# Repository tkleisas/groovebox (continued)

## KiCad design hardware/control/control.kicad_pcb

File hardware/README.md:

# NSR-1 hardware — rev B2

**NSR-1 is the active hardware target.** NSR-2 is a deferred reference
design. The platform mission, support tiers, and the separate-carrier-per-SBC
policy are in [`../docs/mission.md`](../docs/mission.md).

The NSR-1 platform has four boards:

| Board | Spec | Status |
|---|---|---|
| Keyboard | [`netlist-spec.md`](netlist-spec.md) | routed, 0 DRC, EMD-verified |
| Control | [`netlist-spec.md`](netlist-spec.md) | routed, 0 DRC, EMD-verified |
| Brain carrier (Pi Zero 2W) | [`brain/netlist-spec.md`](brain/netlist-spec.md) | 110 × 90, routed, 0 unconnected, 4× M3 |
| Power/battery | [`power/netlist-spec.md`](power/netlist-spec.md) | 100 × 70, 4-layer, routed except 4 airwires |

The control and keyboard boards are the existing rev B2 design. The brain
carrier and power board are new platform boards; their specs are the source of
truth for those boards. A future SBC gets its own carrier under `hardware/`,
not an adapter on the Pi carrier.

This hardware is imported and packaged by
[ElectroMechanicalDesigner](https://github.com/tkleisas/ElectroMechanicalDesigner);
see [`../README.md`](../README.md#electromechanicaldesigner-integration) and
`hardware/tools/verify_emd.py`.

Source of truth for the control/keyboard: [`netlist-spec.md`](netlist-spec.md).
The firmware contract is `panel-fw/src/board_config.h`; change both together.

## Generated schematics

The control and keyboard schematics are generated. Do not hand-edit the
`.kicad_sch` files while the generator is active; change the generator and
regenerate.

```bash
python3 hardware/tools/gen_schematics.py control keyboard brain
python3 hardware/tools/verify_schematics.py
# In the KiCad 10 container:
python3 hardware/tools/place_control.py
python3 hardware/tools/place_keyboard.py
python3 hardware/tools/add_ground_pour.py control
python3 hardware/tools/add_ground_pour.py keyboard
python3 hardware/tools/verify_fit.py
# New platform outlines (run in the KiCad container):
python3 hardware/tools/make_platform_outlines.py
# Add header/connector silkscreen labels once, after routing:
python3 hardware/tools/add_board_labels.py control keyboard brain power
```

`gen_schematics.py` uses the KiCad 10 symbol definitions embedded in the
checked-in NSR-2 schematics for control/keyboard/brain. The power board also
needs the installed KiCad symbol libraries, so generate it inside the KiCad
container with `-e KICAD_SYMBOL_DIR=/usr/share/kicad/symbols`.
`verify_schematics.py` checks pin coverage, key/encoder/analog nets, I²C
endpoints, address straps, LED ROW/COM grouping, and power endpoints.

Export netlists and validate them with EMD:

```bash
python3 hardware/tools/export_netlist.py
# power netlist needs the KiCad symbol directory:
docker run --rm -v "$PWD:/work" -w /work \
  -e KICAD_SYMBOL_DIR=/usr/share/kicad/symbols kicad/kicad:10.0 \
  python3 hardware/tools/export_netlist.py --board power
python3 hardware/tools/verify_emd.py --emd /path/to/emd
python3 hardware/tools/verify_emd.py --package-dir hardware/emd-packages \
  --combined hardware/emd-packages/groovebox.json
```

Check the firmware map against the five-expander contract:

```bash
gcc -std=c11 -Ipanel-fw/src hardware/tools/check_board_config.c -o /tmp/check_board_config
/tmp/check_board_config
```

The control/keyboard board outlines are rev B2: control 130 × 100 mm,
keyboard 356 × 80 mm. Both boards are placed, routed, and checked. The MX
hot-swap footprint is vendored from the keyswitch-kicad-library (`nsr1_fp`,
CC-BY-SA 4.0) and is assigned to all 45 switch symbols.

The brain carrier is the first SBC-specific board. It is a Raspberry Pi Zero
2W carrier by design; Radxa Zero 3W and Orange Pi Zero 3W would each get a
separate carrier and validation effort. The power board is common to all
carriers. Brain carrier: 110 × 90 mm, routed, 0 unconnected, EMD-valid
netlist. Power board: 100 × 70 mm, 4-layer, routed except four rev A airwires
(two BAT_NEG, two SCL). Start from their netlist specs.

The Pico uses `Module:RaspberryPi_Pico_Common_THT` (2×20, 17.78 mm row
spacing, four mounting holes). The Pi Zero uses
`Module:Raspberry_Pi_Zero_Socketed_THT_FaceDown_MountingHoles` (2×20, 2.54 mm
row spacing, mounting holes). Both headers carry silkscreen pin numbers; the
Pico also carries GPIO names.

## KiCad checks

With KiCad 10 in Docker:

```bash
docker run --rm -v "$PWD:/work" -w /work kicad/kicad:10.0 \
  kicad-cli sch erc hardware/control/control.kicad_sch \
  --output /work/control-erc.json --format json --severity-all
```

Current result: **0 ERC errors** for control, keyboard, brain, and power.
Expected warnings are `lib_symbol_mismatch` from the embedded symbol copies
(cosmetic). Routed control/keyboard/brain DRC is clean with 0 unconnected
items; the power board is routed except four rev A airwires (two `BAT_NEG`, two `SCL`).

Generate Gerbers, drill files, position CSV, BOM, STEP, stats, and zip
archives with:

```bash
hardware/tools/export_fabrication.sh
```

Outputs land in `hardware/fabrication/` and are gitignored; regenerate them
from the routed boards when needed. The STEP export defaults to a board-only
model because the KiCad container does not ship the 3D model library. Set
`STEP_FLAGS="--subst-models"` when `kicad-packages3d` is mounted or installed.

## Current scope

- **Control board:** Pico, 2× ADS1115, 2× MCP23017, 8 encoder connectors,
  CUT/RES pots, slider, joystick, 10 function-key connectors, joystick switch,
  keyboard/UART links.
- **Keyboard board:** 45 MX hot-swap sockets (29 piano/shift + 16 step row),
  3× MCP23017, HT16K33, 32 LEDs.
- **Control board:** placed and routed with 0 DRC violations and 0 unconnected
  items. Routing was done with Freerouting 2.5 via Specctra DSN/SES at
  0.15 mm clearance and a 0.1 mm minimum track width; the board grew to 130 × 100 mm to
  clear the eight encoder headers. Four M3 mounting-hole footprints are
  present for EMD mechanical ports.
- **Keyboard board:** all 45 switches, 32 LEDs, 32 resistors, 3 key expanders,
  HT16K33, link, and decoupling placed with
  `hardware/tools/place_keyboard.py`, then routed with Freerouting; DRC
  reports 0 violations and 0 unconnected items. Four M3 mounting-hole
  footprints are present for EMD mechanical ports.
- **Ground pour:** control, keyboard, brain, and power boards have a filled
  B.Cu GND zone.
- **Brain carrier:** Raspberry Pi Zero 2W carrier rev A is 110 × 90 mm,
  routed with 0 unconnected items, 0 ERC errors, and an EMD-valid netlist.
  See [`brain/netlist-spec.md`](brain/netlist-spec.md). It owns the Pi socket,
  Audio Injector Zero stack, display header, DIN MIDI, panel USB breakout, and
  5V input. It deliberately does not contain the battery charger or boost.
- **Power/battery board:** 100 × 70 mm, 4-layer, schematic generated and
  routed except four rev A airwires (two BAT_NEG, two SCL); see
  [`power/netlist-spec.md`](power/netlist-spec.md). It owns USB-C charging,
  1S pack protection/gauging, power switching, and the 5V/3A rail.
- **Mechanical envelope:** see [`enclosure-spec.md`](enclosure-spec.md);
  the 356 × 80 mm keyboard and under-mounted 130 × 100 mm control board fit the
  400 × 170 mm panel, with a ~32 mm internal stack. `verify_fit.py` checks this.
- **EMD package:** the combined project imports all four netlists/PCBs
  (control, keyboard, brain carrier, power), places them in the 400 × 170 mm
  envelope, validates 237 parts / 735 connections, and produces a verified
  package.
- **Enclosure:** printable tray and cutout faceplate are in
  [`enclosure/`](enclosure/README.md); rear I/O openings remain.
- **Power/thermal:** see [`power-thermal-review.md`](power-thermal-review.md).

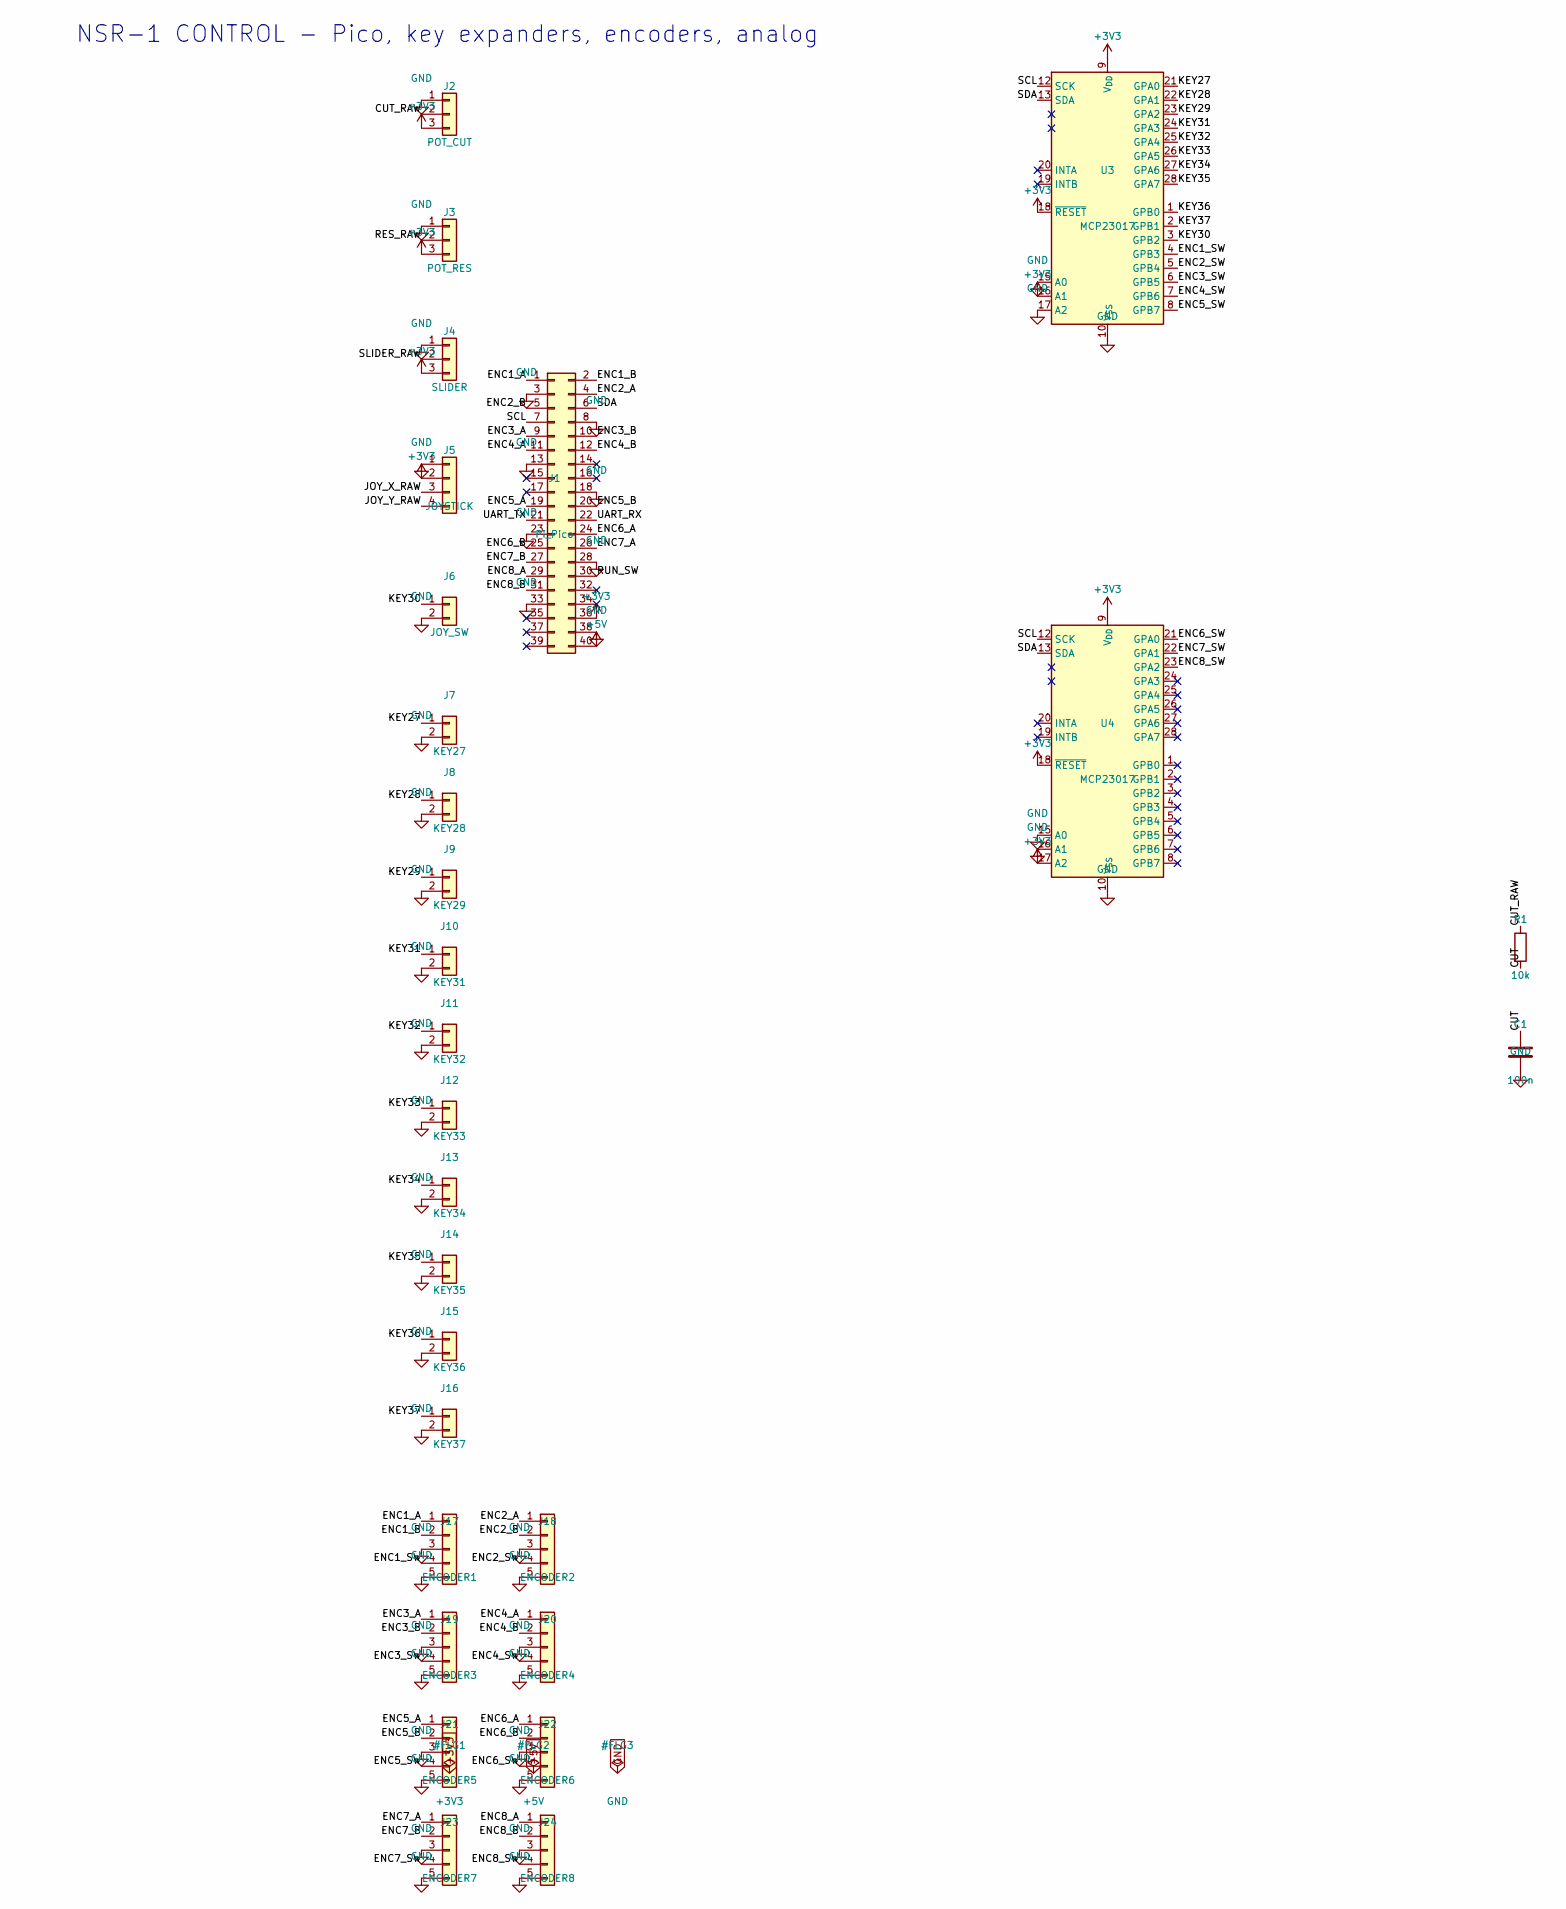
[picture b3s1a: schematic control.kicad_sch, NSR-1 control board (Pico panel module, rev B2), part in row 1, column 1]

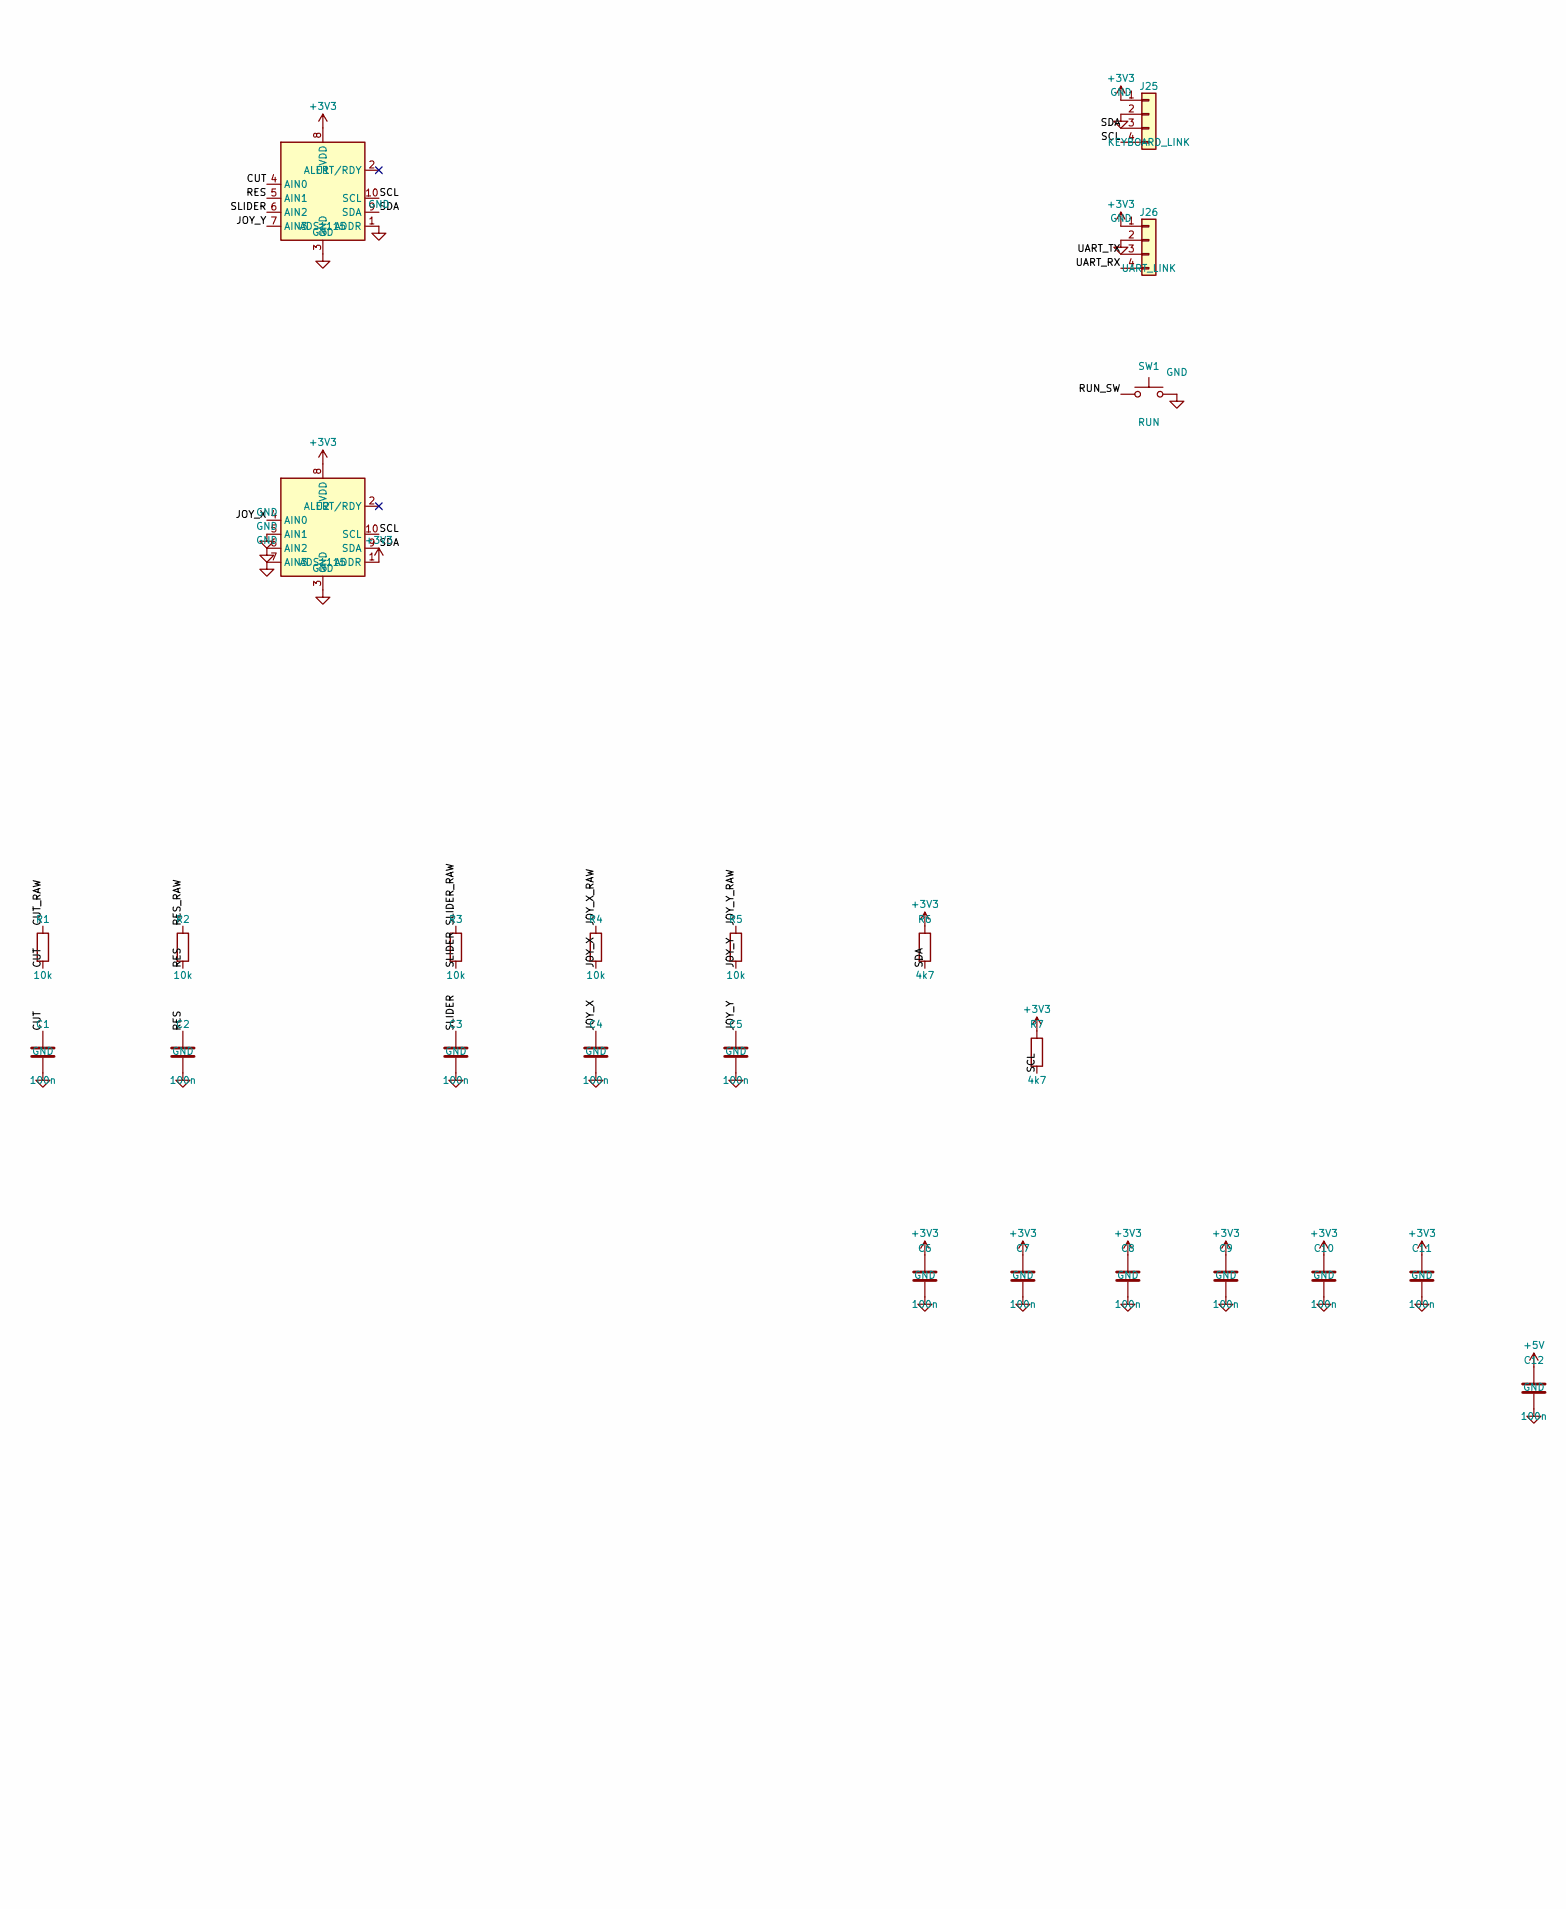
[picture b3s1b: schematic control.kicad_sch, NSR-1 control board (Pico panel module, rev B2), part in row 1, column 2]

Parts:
C1, C2, C3, C4, C5, C6, C7, C8, C9, C10, C11, C12: 100n; C_0805_2012Metric
J1: Pi_Pico; RaspberryPi_Pico_Common_THT
J2: POT_CUT; JST_XH_B3B-XH-A_1x03_P2.50mm_Vertical
J3: POT_RES; JST_XH_B3B-XH-A_1x03_P2.50mm_Vertical
J4: SLIDER; JST_XH_B3B-XH-A_1x03_P2.50mm_Vertical
J5: JOYSTICK; JST_XH_B4B-XH-A_1x04_P2.50mm_Vertical
J6: JOY_SW; JST_XH_B2B-XH-A_1x02_P2.50mm_Vertical
J7: KEY27; JST_XH_B2B-XH-A_1x02_P2.50mm_Vertical
J8: KEY28; JST_XH_B2B-XH-A_1x02_P2.50mm_Vertical
J9: KEY29; JST_XH_B2B-XH-A_1x02_P2.50mm_Vertical
J10: KEY31; JST_XH_B2B-XH-A_1x02_P2.50mm_Vertical
J11: KEY32; JST_XH_B2B-XH-A_1x02_P2.50mm_Vertical
J12: KEY33; JST_XH_B2B-XH-A_1x02_P2.50mm_Vertical
J13: KEY34; JST_XH_B2B-XH-A_1x02_P2.50mm_Vertical
J14: KEY35; JST_XH_B2B-XH-A_1x02_P2.50mm_Vertical
J15: KEY36; JST_XH_B2B-XH-A_1x02_P2.50mm_Vertical
J16: KEY37; JST_XH_B2B-XH-A_1x02_P2.50mm_Vertical
J17: ENCODER1; JST_XH_B5B-XH-A_1x05_P2.50mm_Vertical
J18: ENCODER2; JST_XH_B5B-XH-A_1x05_P2.50mm_Vertical
J19: ENCODER3; JST_XH_B5B-XH-A_1x05_P2.50mm_Vertical
J20: ENCODER4; JST_XH_B5B-XH-A_1x05_P2.50mm_Vertical
J21: ENCODER5; JST_XH_B5B-XH-A_1x05_P2.50mm_Vertical
J22: ENCODER6; JST_XH_B5B-XH-A_1x05_P2.50mm_Vertical
J23: ENCODER7; JST_XH_B5B-XH-A_1x05_P2.50mm_Vertical
J24: ENCODER8; JST_XH_B5B-XH-A_1x05_P2.50mm_Vertical
J25: KEYBOARD_LINK; JST_XH_B4B-XH-A_1x04_P2.50mm_Vertical
J26: UART_LINK; JST_XH_B4B-XH-A_1x04_P2.50mm_Vertical
R1, R2, R3, R4, R5: 10k; R_0805_2012Metric
R6, R7: 4k7; R_0805_2012Metric
SW1: RUN; SW_PUSH_6mm
U1, U2: ADS1115; MSOP-10_3x3mm_P0.5mm
U3, U4: MCP23017; SSOP-28_5.3x10.2mm_P0.65mm

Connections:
+3V3: C6.1, C7.1, C8.1, C9.1, C10.1, C11.1, J1.36, J2.3, J3.3, J4.3, J5.2, J25.1, J26.1, R6.1, R7.1, U1.8 (VDD), U2.1 (ADDR), U2.8 (VDD), U3.9 (V_{DD}), U3.16 (A1), U3.18 (~RESET), U4.9 (V_{DD}), U4.17 (A2), U4.18 (~RESET)
+5V: C12.1, J1.40
CUT: C1.1, R1.2, U1.4 (AIN0)
CUT_RAW: J2.2, R1.1
ENC1_A: J1.1, J17.1
ENC1_B: J1.2, J17.2
ENC1_SW: J17.4, U3.4 (GPB3)
ENC2_A: J1.4, J18.1
ENC2_B: J1.5, J18.2
ENC2_SW: J18.4, U3.5 (GPB4)
ENC3_A: J1.9, J19.1
ENC3_B: J1.10, J19.2
ENC3_SW: J19.4, U3.6 (GPB5)
ENC4_A: J1.11, J20.1
ENC4_B: J1.12, J20.2
ENC4_SW: J20.4, U3.7 (GPB6)
ENC5_A: J1.19, J21.1
ENC5_B: J1.20, J21.2
ENC5_SW: J21.4, U3.8 (GPB7)
ENC6_A: J1.24, J22.1
ENC6_B: J1.25, J22.2
ENC6_SW: J22.4, U4.21 (GPA0)
ENC7_A: J1.26, J23.1
ENC7_B: J1.27, J23.2
ENC7_SW: J23.4, U4.22 (GPA1)
ENC8_A: J1.29, J24.1
ENC8_B: J1.31, J24.2
ENC8_SW: J24.4, U4.23 (GPA2)
GND: C1.2, C2.2, C3.2, C4.2, C5.2, C6.2, C7.2, C8.2, C9.2, C10.2, C11.2, C12.2, J1.3, J1.8, J1.13, J1.18, J1.23, J1.28, J1.33, J1.38, J2.1, J3.1, J4.1, J5.1, J6.2, J7.2, J8.2, J9.2, J10.2, J11.2, J12.2, J13.2, J14.2, J15.2, J16.2, J17.3, J17.5, J18.3, J18.5, J19.3, J19.5, J20.3, J20.5, J21.3, J21.5, J22.3, J22.5, J23.3, J23.5, J24.3, J24.5, J25.2, J26.2, SW1.2, U1.1 (ADDR), U1.3 (GND), U2.3 (GND), U2.5 (AIN1), U2.6 (AIN2), U2.7 (AIN3), U3.10 (V_{SS}), U3.15 (A0), U3.17 (A2), U4.10 (V_{SS}), U4.15 (A0), U4.16 (A1)
JOY_X: C4.1, R4.2, U2.4 (AIN0)
JOY_X_RAW: J5.3, R4.1
JOY_Y: C5.1, R5.2, U1.7 (AIN3)
JOY_Y_RAW: J5.4, R5.1
KEY27: J7.1, U3.21 (GPA0)
KEY28: J8.1, U3.22 (GPA1)
KEY29: J9.1, U3.23 (GPA2)
KEY30: J6.1, U3.3 (GPB2)
KEY31: J10.1, U3.24 (GPA3)
KEY32: J11.1, U3.25 (GPA4)
KEY33: J12.1, U3.26 (GPA5)
KEY34: J13.1, U3.27 (GPA6)
KEY35: J14.1, U3.28 (GPA7)
KEY36: J15.1, U3.1 (GPB0)
KEY37: J16.1, U3.2 (GPB1)
RES: C2.1, R2.2, U1.5 (AIN1)
RES_RAW: J3.2, R2.1
RUN_SW: J1.30, SW1.1
SCL: J1.7, J25.4, R7.2, U1.10 (SCL), U2.10 (SCL), U3.12 (SCK), U4.12 (SCK)
SDA: J1.6, J25.3, R6.2, U1.9 (SDA), U2.9 (SDA), U3.13 (SDA), U4.13 (SDA)
SLIDER: C3.1, R3.2, U1.6 (AIN2)
SLIDER_RAW: J4.2, R3.1
UART_RX: J1.22, J26.4
UART_TX: J1.21, J26.3

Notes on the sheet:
NSR-1 CONTROL - Pico, key expanders, encoders, analog

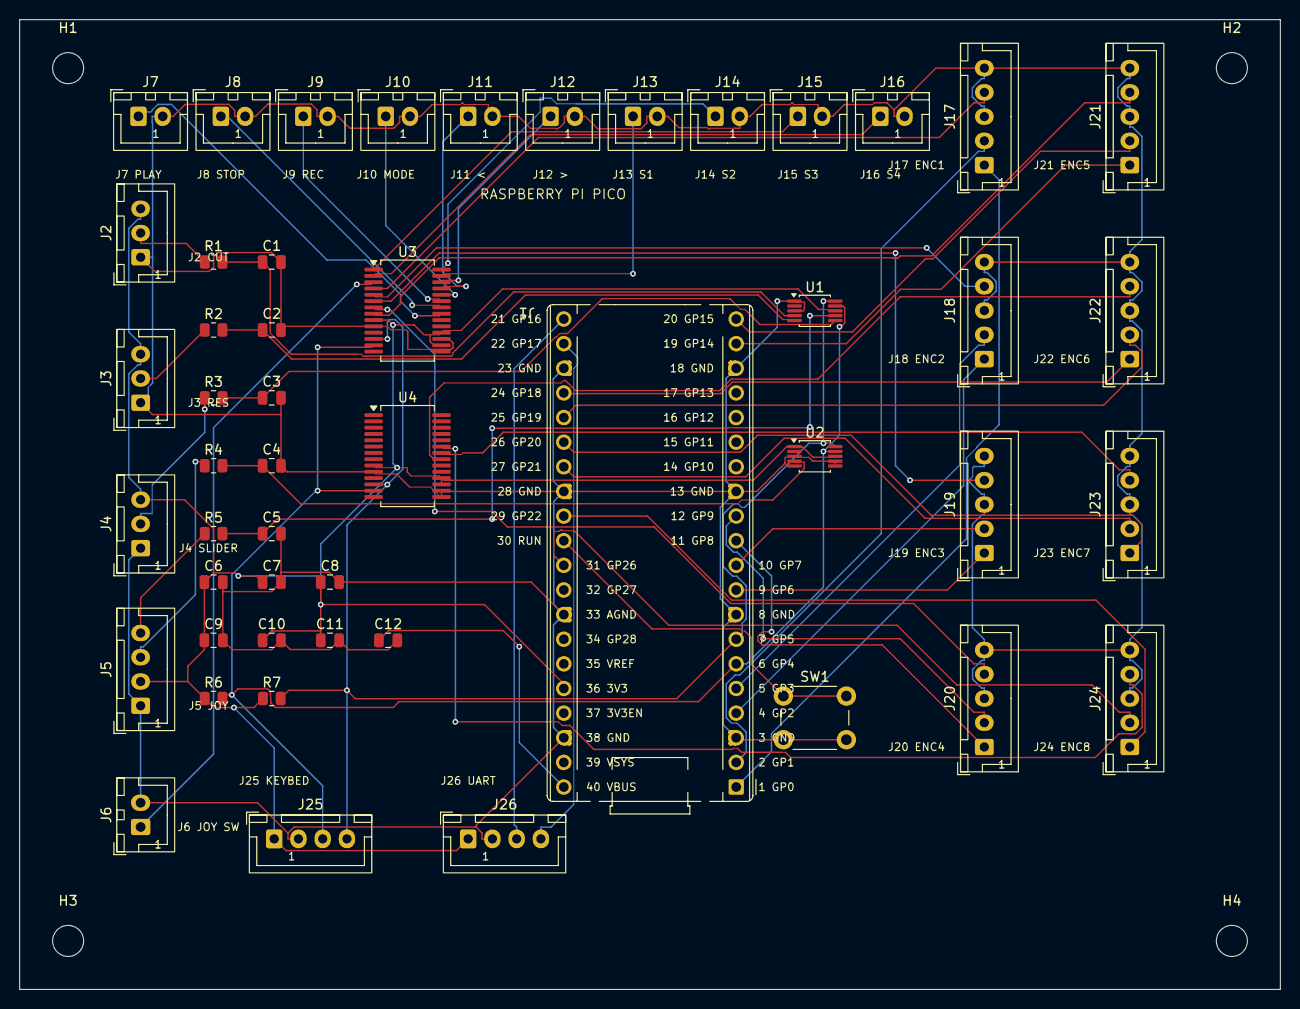
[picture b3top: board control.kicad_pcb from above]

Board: 2 copper layers, 130.0 x 100.0 mm, 54 parts (0 on the bottom side), 53 nets.

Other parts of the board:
H1, H2, H3, H4: MountingHole_3.2mm_M3

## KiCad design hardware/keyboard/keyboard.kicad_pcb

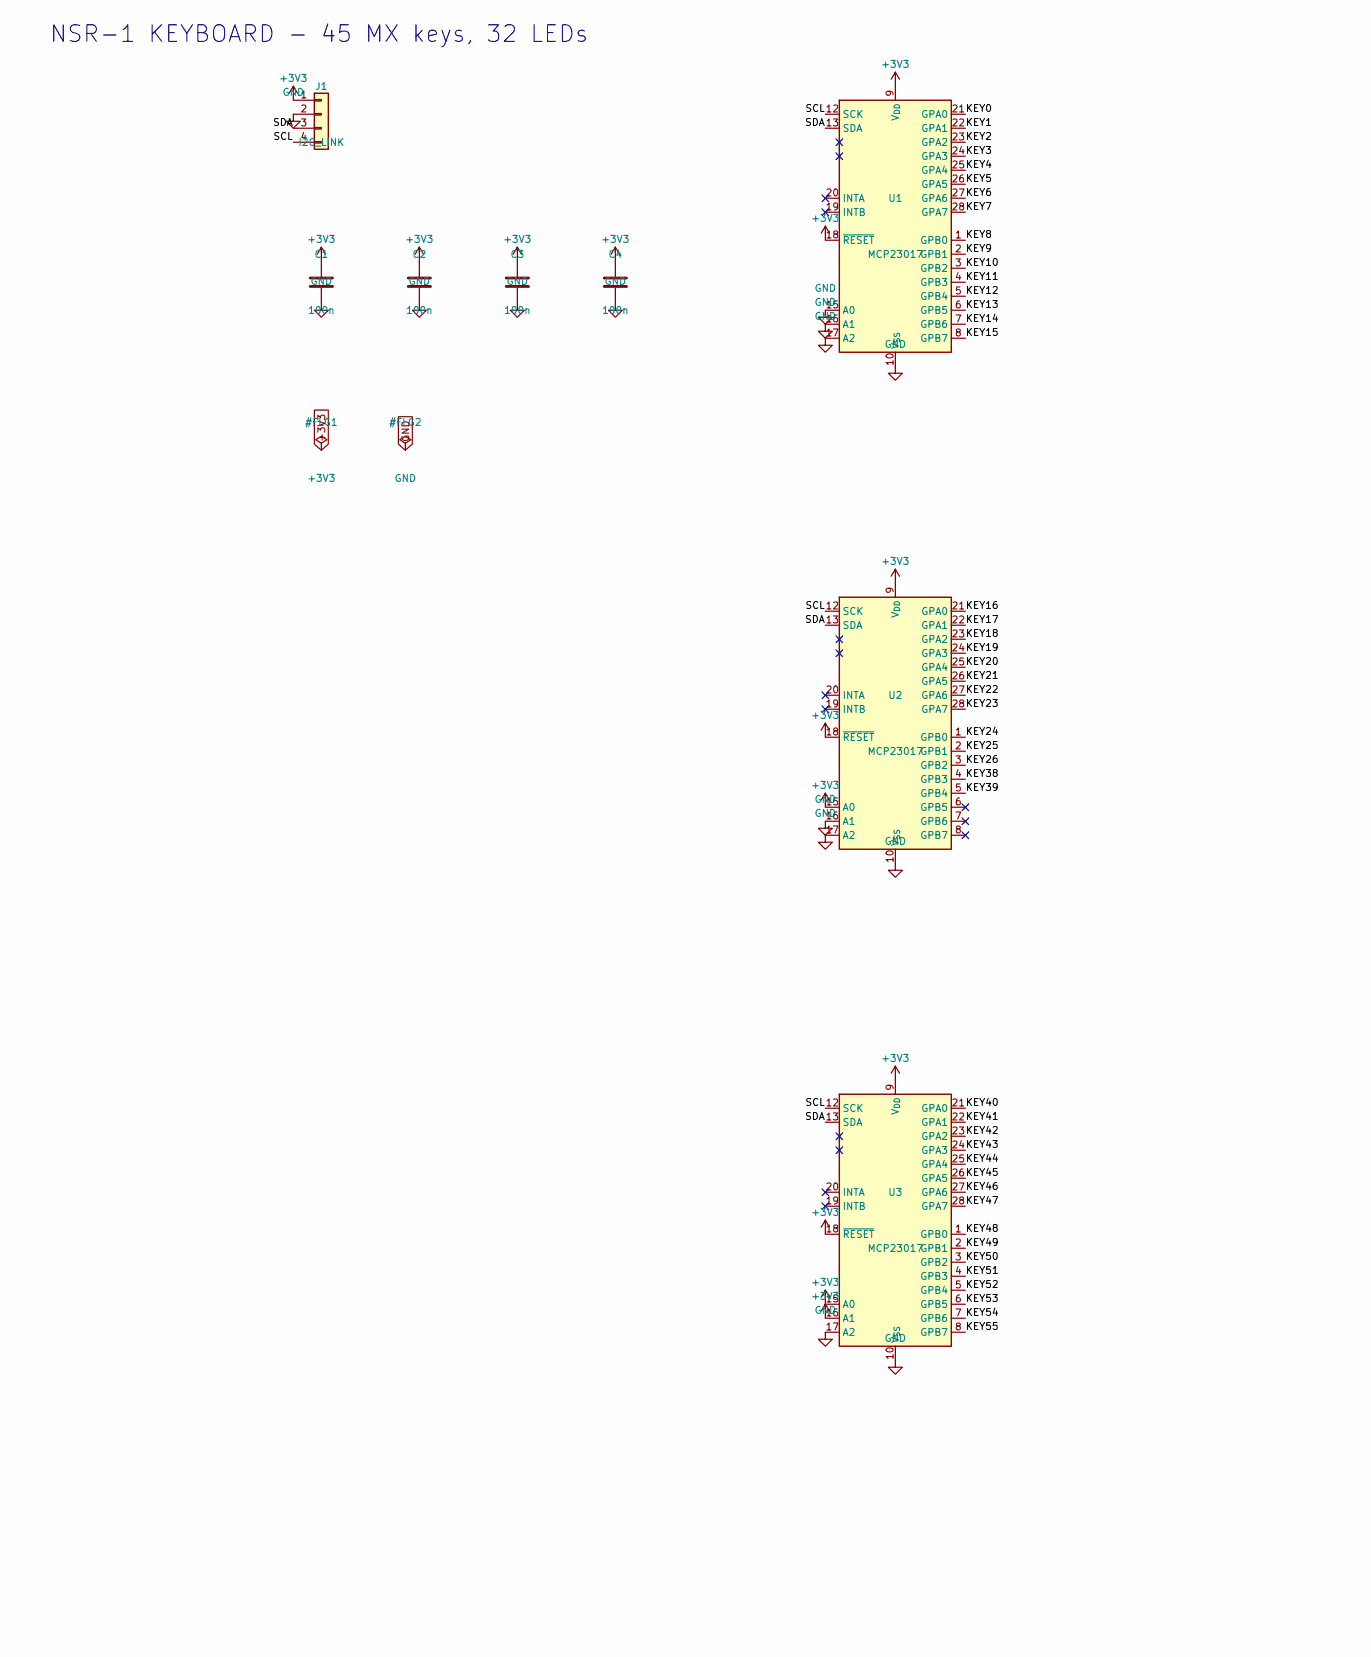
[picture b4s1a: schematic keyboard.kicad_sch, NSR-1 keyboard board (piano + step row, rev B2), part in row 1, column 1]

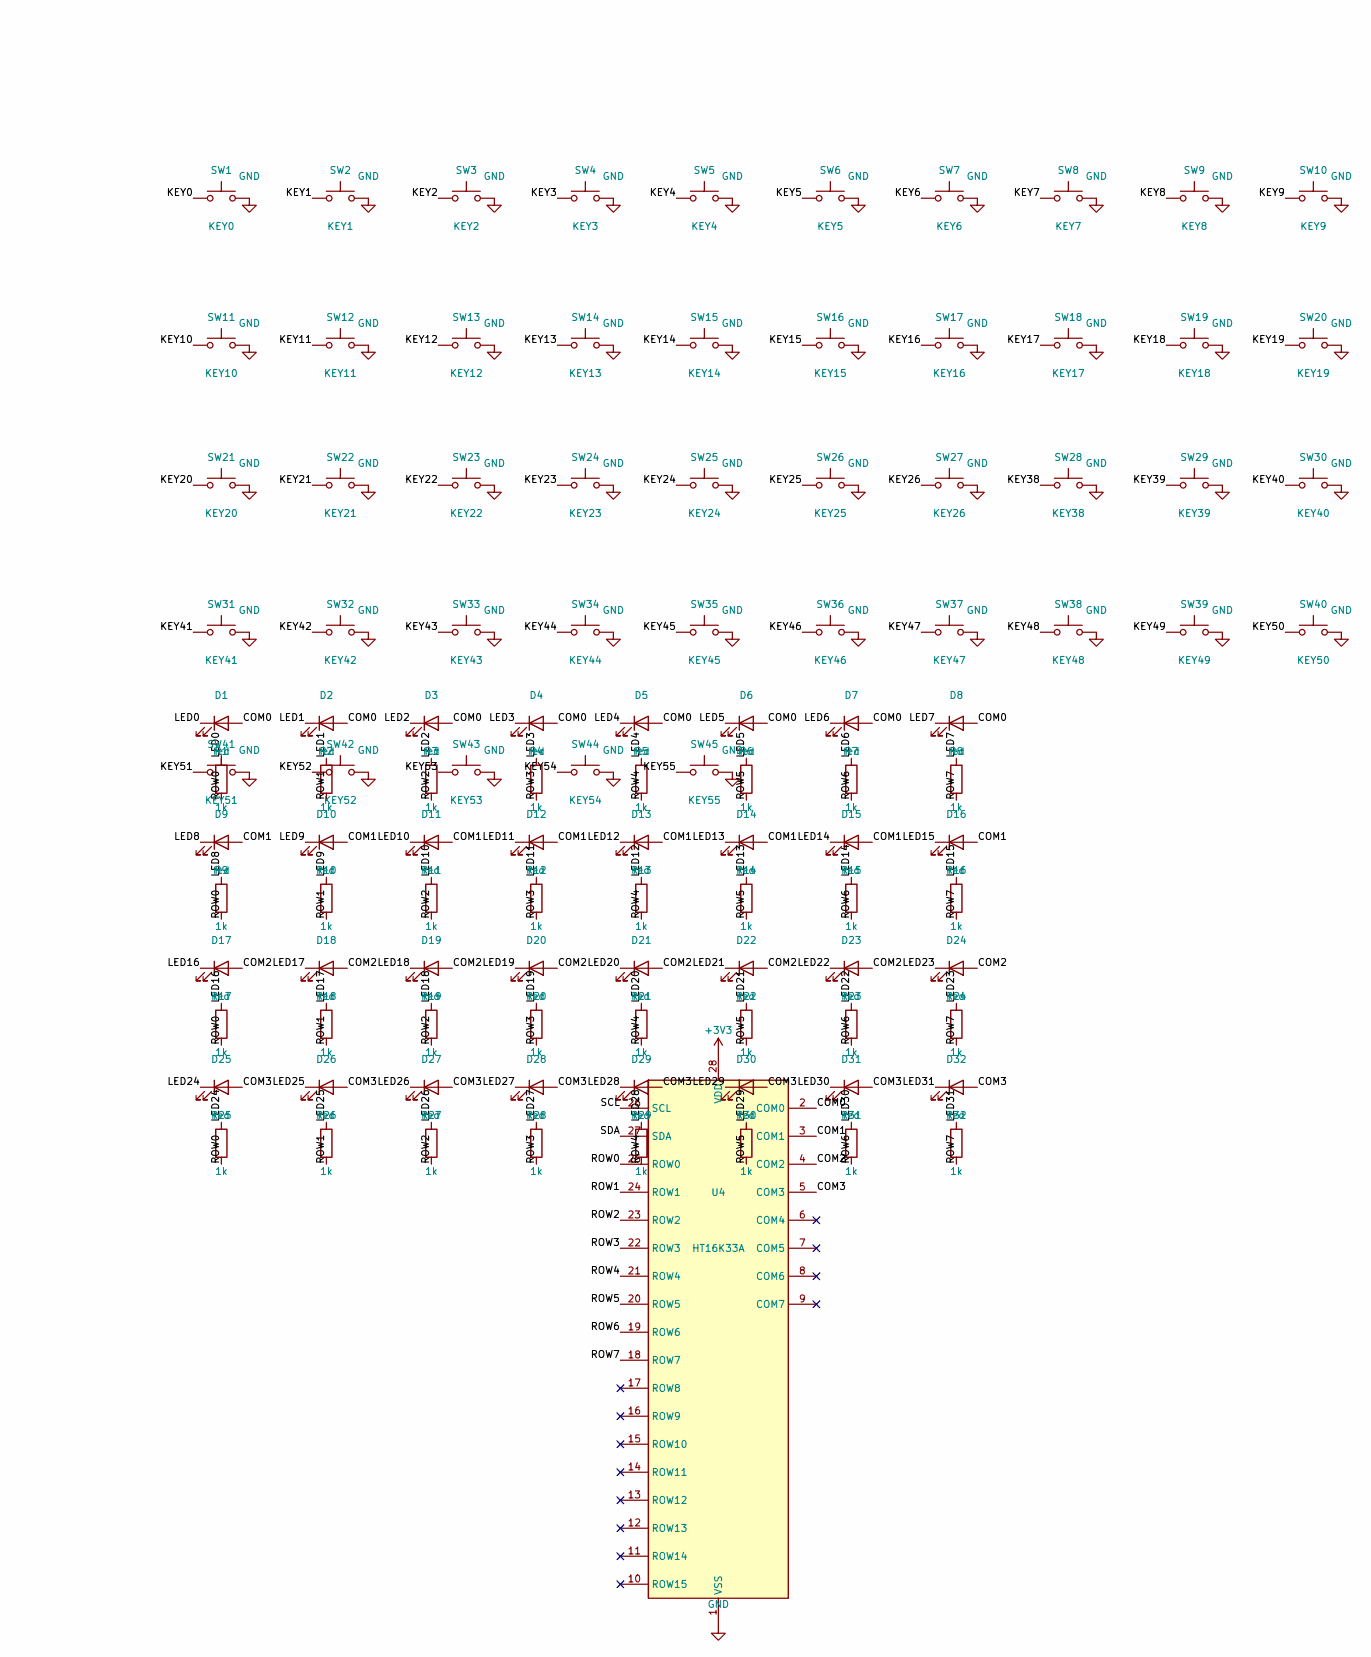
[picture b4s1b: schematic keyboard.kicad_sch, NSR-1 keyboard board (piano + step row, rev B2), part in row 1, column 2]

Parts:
C1, C2, C3, C4: 100n; C_0805_2012Metric
D1, D2, D3, D4, D5, D6, D7, D8, D9, D10, D11, D12, D13, D14, D15, D16, D17, D18, D19, D20, D21, D22, D23, D24, D25, D26, D27, D28, D29, D30, D31, D32: red; LED_D3.0mm
J1: I2C_LINK; JST_XH_B4B-XH-A_1x04_P2.50mm_Vertical
R1, R2, R3, R4, R5, R6, R7, R8, R9, R10, R11, R12, R13, R14, R15, R16, R17, R18, R19, R20, R21, R22, R23, R24, R25, R26, R27, R28, R29, R30, R31, R32: 1k; R_0805_2012Metric
SW1: KEY0; SW_Hotswap_Kailh_MX_Plated_1.00u
SW2: KEY1; SW_Hotswap_Kailh_MX_Plated_1.00u
SW3: KEY2; SW_Hotswap_Kailh_MX_Plated_1.00u
SW4: KEY3; SW_Hotswap_Kailh_MX_Plated_1.00u
SW5: KEY4; SW_Hotswap_Kailh_MX_Plated_1.00u
SW6: KEY5; SW_Hotswap_Kailh_MX_Plated_1.00u
SW7: KEY6; SW_Hotswap_Kailh_MX_Plated_1.00u
SW8: KEY7; SW_Hotswap_Kailh_MX_Plated_1.00u
SW9: KEY8; SW_Hotswap_Kailh_MX_Plated_1.00u
SW10: KEY9; SW_Hotswap_Kailh_MX_Plated_1.00u
SW11: KEY10; SW_Hotswap_Kailh_MX_Plated_1.00u
SW12: KEY11; SW_Hotswap_Kailh_MX_Plated_1.00u
SW13: KEY12; SW_Hotswap_Kailh_MX_Plated_1.00u
SW14: KEY13; SW_Hotswap_Kailh_MX_Plated_1.00u
SW15: KEY14; SW_Hotswap_Kailh_MX_Plated_1.00u
SW16: KEY15; SW_Hotswap_Kailh_MX_Plated_1.00u
SW17: KEY16; SW_Hotswap_Kailh_MX_Plated_1.00u
SW18: KEY17; SW_Hotswap_Kailh_MX_Plated_1.00u
SW19: KEY18; SW_Hotswap_Kailh_MX_Plated_1.00u
SW20: KEY19; SW_Hotswap_Kailh_MX_Plated_1.00u
SW21: KEY20; SW_Hotswap_Kailh_MX_Plated_1.00u
SW22: KEY21; SW_Hotswap_Kailh_MX_Plated_1.00u
SW23: KEY22; SW_Hotswap_Kailh_MX_Plated_1.00u
SW24: KEY23; SW_Hotswap_Kailh_MX_Plated_1.00u
SW25: KEY24; SW_Hotswap_Kailh_MX_Plated_1.00u
SW26: KEY25; SW_Hotswap_Kailh_MX_Plated_1.00u
SW27: KEY26; SW_Hotswap_Kailh_MX_Plated_1.00u
SW28: KEY38; SW_Hotswap_Kailh_MX_Plated_1.00u
SW29: KEY39; SW_Hotswap_Kailh_MX_Plated_1.00u
SW30: KEY40; SW_Hotswap_Kailh_MX_Plated_1.00u
SW31: KEY41; SW_Hotswap_Kailh_MX_Plated_1.00u
SW32: KEY42; SW_Hotswap_Kailh_MX_Plated_1.00u
SW33: KEY43; SW_Hotswap_Kailh_MX_Plated_1.00u
SW34: KEY44; SW_Hotswap_Kailh_MX_Plated_1.00u
SW35: KEY45; SW_Hotswap_Kailh_MX_Plated_1.00u
SW36: KEY46; SW_Hotswap_Kailh_MX_Plated_1.00u
SW37: KEY47; SW_Hotswap_Kailh_MX_Plated_1.00u
SW38: KEY48; SW_Hotswap_Kailh_MX_Plated_1.00u
SW39: KEY49; SW_Hotswap_Kailh_MX_Plated_1.00u
SW40: KEY50; SW_Hotswap_Kailh_MX_Plated_1.00u
SW41: KEY51; SW_Hotswap_Kailh_MX_Plated_1.00u
SW42: KEY52; SW_Hotswap_Kailh_MX_Plated_1.00u
SW43: KEY53; SW_Hotswap_Kailh_MX_Plated_1.00u
SW44: KEY54; SW_Hotswap_Kailh_MX_Plated_1.00u
SW45: KEY55; SW_Hotswap_Kailh_MX_Plated_1.00u
U1, U2, U3: MCP23017; SSOP-28_5.3x10.2mm_P0.65mm
U4: HT16K33A; SSOP-28_5.3x10.2mm_P0.65mm

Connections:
+3V3: C1.1, C2.1, C3.1, C4.1, J1.1, U1.9 (V_{DD}), U1.18 (~RESET), U2.9 (V_{DD}), U2.15 (A0), U2.18 (~RESET), U3.9 (V_{DD}), U3.15 (A0), U3.16 (A1), U3.18 (~RESET), U4.28 (VDD)
COM0: D1.2 (A), D2.2 (A), D3.2 (A), D4.2 (A), D5.2 (A), D6.2 (A), D7.2 (A), D8.2 (A), U4.2 (COM0)
COM1: D9.2 (A), D10.2 (A), D11.2 (A), D12.2 (A), D13.2 (A), D14.2 (A), D15.2 (A), D16.2 (A), U4.3 (COM1)
COM2: D17.2 (A), D18.2 (A), D19.2 (A), D20.2 (A), D21.2 (A), D22.2 (A), D23.2 (A), D24.2 (A), U4.4 (COM2)
COM3: D25.2 (A), D26.2 (A), D27.2 (A), D28.2 (A), D29.2 (A), D30.2 (A), D31.2 (A), D32.2 (A), U4.5 (COM3)
GND: C1.2, C2.2, C3.2, C4.2, J1.2, SW1.2, SW2.2, SW3.2, SW4.2, SW5.2, SW6.2, SW7.2, SW8.2, SW9.2, SW10.2, SW11.2, SW12.2, SW13.2, SW14.2, SW15.2, SW16.2, SW17.2, SW18.2, SW19.2, SW20.2, SW21.2, SW22.2, SW23.2, SW24.2, SW25.2, SW26.2, SW27.2, SW28.2, SW29.2, SW30.2, SW31.2, SW32.2, SW33.2, SW34.2, SW35.2, SW36.2, SW37.2, SW38.2, SW39.2, SW40.2, SW41.2, SW42.2, SW43.2, SW44.2, SW45.2, U1.10 (V_{SS}), U1.15 (A0), U1.16 (A1), U1.17 (A2), U2.10 (V_{SS}), U2.16 (A1), U2.17 (A2), U3.10 (V_{SS}), U3.17 (A2), U4.1 (VSS)
KEY0: SW1.1, U1.21 (GPA0)
KEY1: SW2.1, U1.22 (GPA1)
KEY2: SW3.1, U1.23 (GPA2)
KEY3: SW4.1, U1.24 (GPA3)
KEY4: SW5.1, U1.25 (GPA4)
KEY5: SW6.1, U1.26 (GPA5)
KEY6: SW7.1, U1.27 (GPA6)
KEY7: SW8.1, U1.28 (GPA7)
KEY8: SW9.1, U1.1 (GPB0)
KEY9: SW10.1, U1.2 (GPB1)
KEY10: SW11.1, U1.3 (GPB2)
KEY11: SW12.1, U1.4 (GPB3)
KEY12: SW13.1, U1.5 (GPB4)
KEY13: SW14.1, U1.6 (GPB5)
KEY14: SW15.1, U1.7 (GPB6)
KEY15: SW16.1, U1.8 (GPB7)
KEY16: SW17.1, U2.21 (GPA0)
KEY17: SW18.1, U2.22 (GPA1)
KEY18: SW19.1, U2.23 (GPA2)
KEY19: SW20.1, U2.24 (GPA3)
KEY20: SW21.1, U2.25 (GPA4)
KEY21: SW22.1, U2.26 (GPA5)
KEY22: SW23.1, U2.27 (GPA6)
KEY23: SW24.1, U2.28 (GPA7)
KEY24: SW25.1, U2.1 (GPB0)
KEY25: SW26.1, U2.2 (GPB1)
KEY26: SW27.1, U2.3 (GPB2)
KEY38: SW28.1, U2.4 (GPB3)
KEY39: SW29.1, U2.5 (GPB4)
KEY40: SW30.1, U3.21 (GPA0)
KEY41: SW31.1, U3.22 (GPA1)
KEY42: SW32.1, U3.23 (GPA2)
KEY43: SW33.1, U3.24 (GPA3)
KEY44: SW34.1, U3.25 (GPA4)
KEY45: SW35.1, U3.26 (GPA5)
KEY46: SW36.1, U3.27 (GPA6)
KEY47: SW37.1, U3.28 (GPA7)
KEY48: SW38.1, U3.1 (GPB0)
KEY49: SW39.1, U3.2 (GPB1)
KEY50: SW40.1, U3.3 (GPB2)
KEY51: SW41.1, U3.4 (GPB3)
KEY52: SW42.1, U3.5 (GPB4)
KEY53: SW43.1, U3.6 (GPB5)
KEY54: SW44.1, U3.7 (GPB6)
KEY55: SW45.1, U3.8 (GPB7)
LED0: D1.1 (K), R1.1
LED1: D2.1 (K), R2.1
LED2: D3.1 (K), R3.1
LED3: D4.1 (K), R4.1
LED4: D5.1 (K), R5.1
LED5: D6.1 (K), R6.1
LED6: D7.1 (K), R7.1
LED7: D8.1 (K), R8.1
LED8: D9.1 (K), R9.1
LED9: D10.1 (K), R10.1
LED10: D11.1 (K), R11.1
LED11: D12.1 (K), R12.1
LED12: D13.1 (K), R13.1
LED13: D14.1 (K), R14.1
LED14: D15.1 (K), R15.1
LED15: D16.1 (K), R16.1
LED16: D17.1 (K), R17.1
LED17: D18.1 (K), R18.1
LED18: D19.1 (K), R19.1
LED19: D20.1 (K), R20.1
LED20: D21.1 (K), R21.1
LED21: D22.1 (K), R22.1
LED22: D23.1 (K), R23.1
LED23: D24.1 (K), R24.1
LED24: D25.1 (K), R25.1
LED25: D26.1 (K), R26.1
LED26: D27.1 (K), R27.1
LED27: D28.1 (K), R28.1
LED28: D29.1 (K), R29.1
LED29: D30.1 (K), R30.1
LED30: D31.1 (K), R31.1
LED31: D32.1 (K), R32.1
ROW0: R1.2, R9.2, R17.2, R25.2, U4.25 (ROW0)
ROW1: R2.2, R10.2, R18.2, R26.2, U4.24 (ROW1)
ROW2: R3.2, R11.2, R19.2, R27.2, U4.23 (ROW2)
ROW3: R4.2, R12.2, R20.2, R28.2, U4.22 (ROW3)
ROW4: R5.2, R13.2, R21.2, R29.2, U4.21 (ROW4)
ROW5: R6.2, R14.2, R22.2, R30.2, U4.20 (ROW5)
ROW6: R7.2, R15.2, R23.2, R31.2, U4.19 (ROW6)
ROW7: R8.2, R16.2, R24.2, R32.2, U4.18 (ROW7)
SCL: J1.4, U1.12 (SCK), U2.12 (SCK), U3.12 (SCK), U4.26 (SCL)
SDA: J1.3, U1.13 (SDA), U2.13 (SDA), U3.13 (SDA), U4.27 (SDA)

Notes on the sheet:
NSR-1 KEYBOARD - 45 MX keys, 32 LEDs

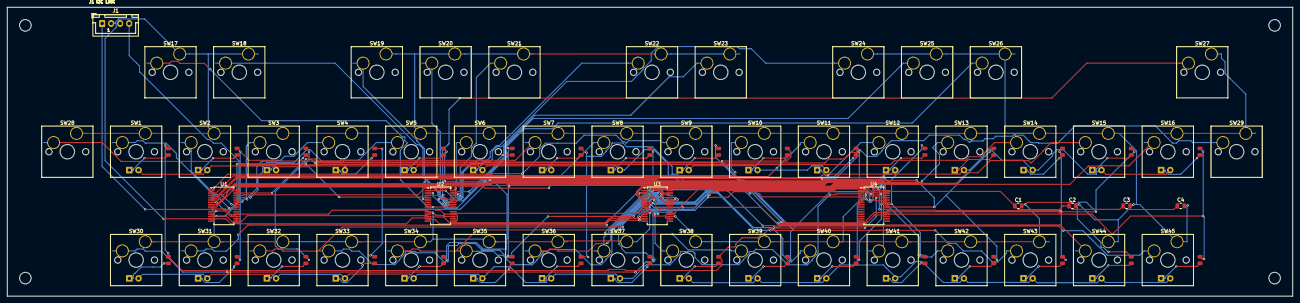
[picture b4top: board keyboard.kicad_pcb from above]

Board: 2 copper layers, 356.0 x 80.0 mm, 122 parts (0 on the bottom side), 93 nets.

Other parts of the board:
H1, H2, H3, H4: MountingHole_3.2mm_M3
